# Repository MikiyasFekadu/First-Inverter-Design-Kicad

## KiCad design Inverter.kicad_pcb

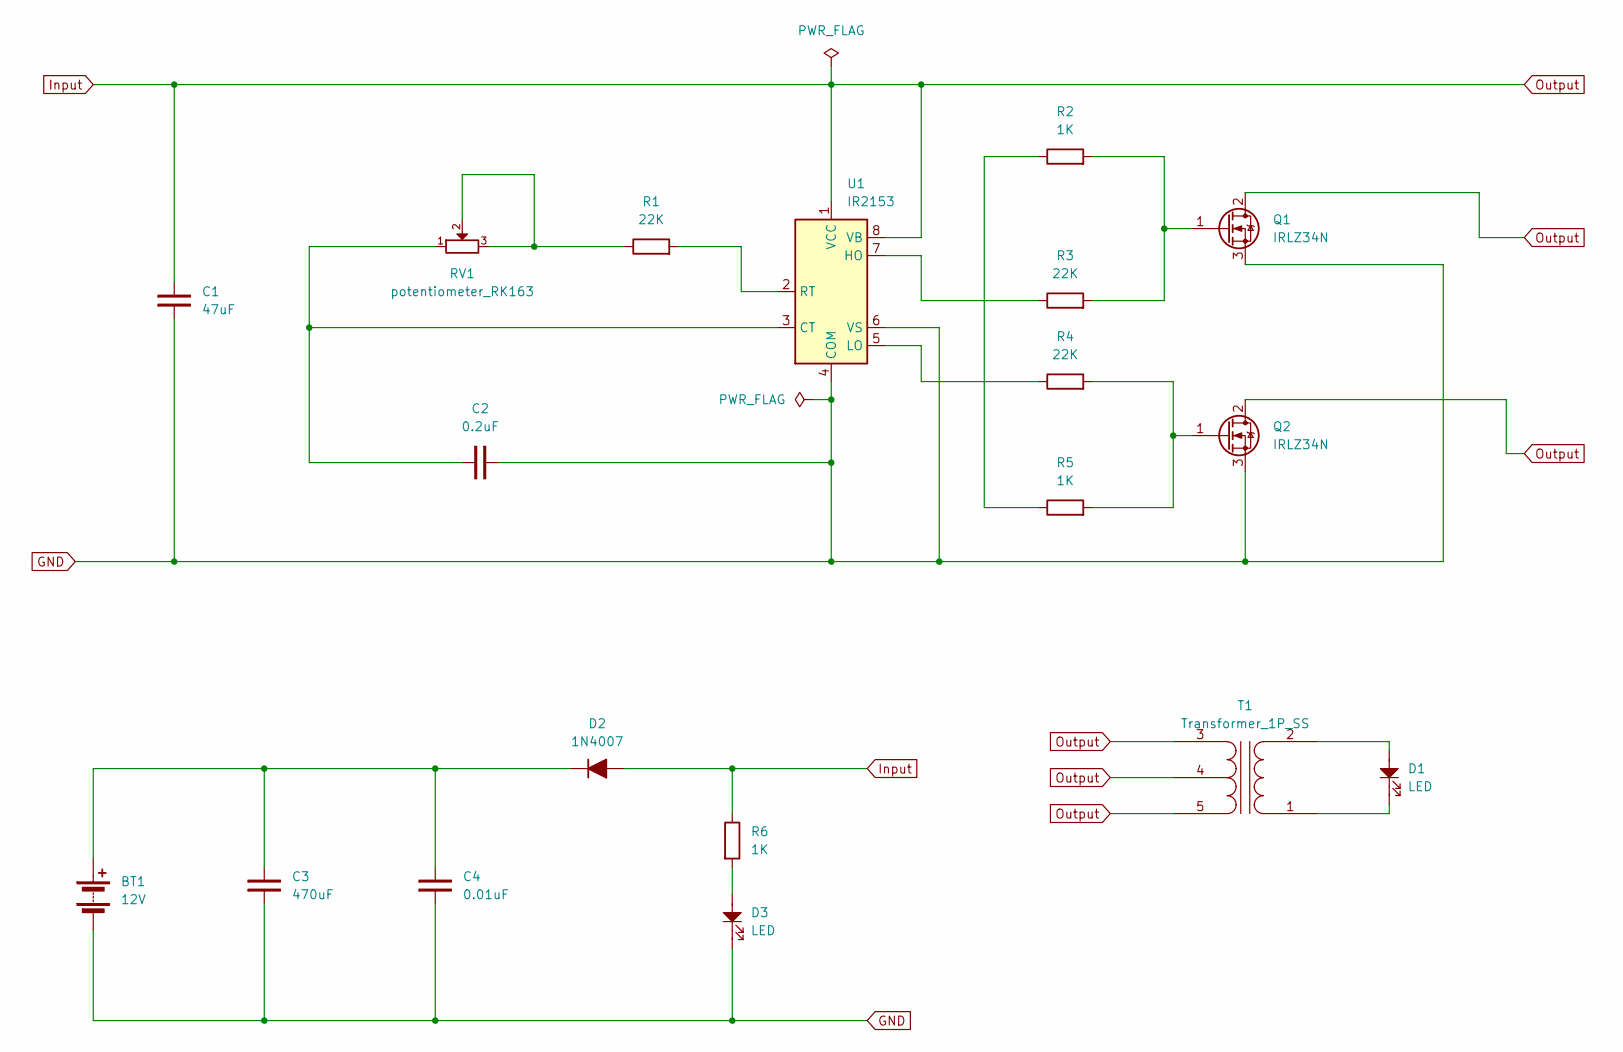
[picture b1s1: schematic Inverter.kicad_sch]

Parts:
BT1: 12V; TerminalBlock_Xinya_XY308-2.54-2P_1x02_P2.54mm_Horizontal
C1: 47uF; CP_Radial_D4.0mm_P1.50mm
C2: 0.2uF; C_Disc_D3.0mm_W2.0mm_P2.50mm
C3: 470uF; CP_Radial_D4.0mm_P1.50mm
C4: 0.01uF; C_Disc_D3.0mm_W2.0mm_P2.50mm
D1, D3: LED; LED_D5.0mm
D2: 1N4007; D_DO-41_SOD81_P10.16mm_Horizontal
Q1, Q2: IRLZ34N; TO-220-3_Vertical
R1, R3, R4: 22K; R_Axial_DIN0204_L3.6mm_D1.6mm_P5.08mm_Horizontal
R2, R5, R6: 1K; R_Axial_DIN0204_L3.6mm_D1.6mm_P5.08mm_Horizontal
RV1: potentiometer_RK163; TRIM_3296W-1-250
T1: Transformer_1P_SS; DIP-8_W7.62mm
U1: IR2153; DIP-8_W7.62mm

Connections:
GND: BT1.2 (-), C1.1, C2.2, C3.1, C4.1, D3.1, Q1.3 (S), Q2.3 (S), U1.4 (COM), U1.6 (VS)
Input: C1.2, D2.2 (A), Q1.2 (D), Q2.2 (D), R6.1, T1.3 (SA), T1.4 (SC), T1.5 (SB), U1.1 (VCC), U1.8 (VB)
unnamed: BT1.1 (+), C3.2, C4.2, D2.1 (K)
unnamed: D3.2, R6.2
unnamed: Q1.1 (G), R2.2, R3.2
unnamed: Q2.1 (G), R4.2, R5.2
unnamed: R1.1, RV1.2, RV1.3
unnamed: R2.1, R5.1
unnamed: D1.1, T1.1 (AA)
unnamed: D1.2, T1.2 (AB)
unnamed: C2.1, RV1.1, U1.3 (CT)
unnamed: R3.1, U1.7 (HO)
unnamed: R4.1, U1.5 (LO)
unnamed: R1.2, U1.2 (RT)

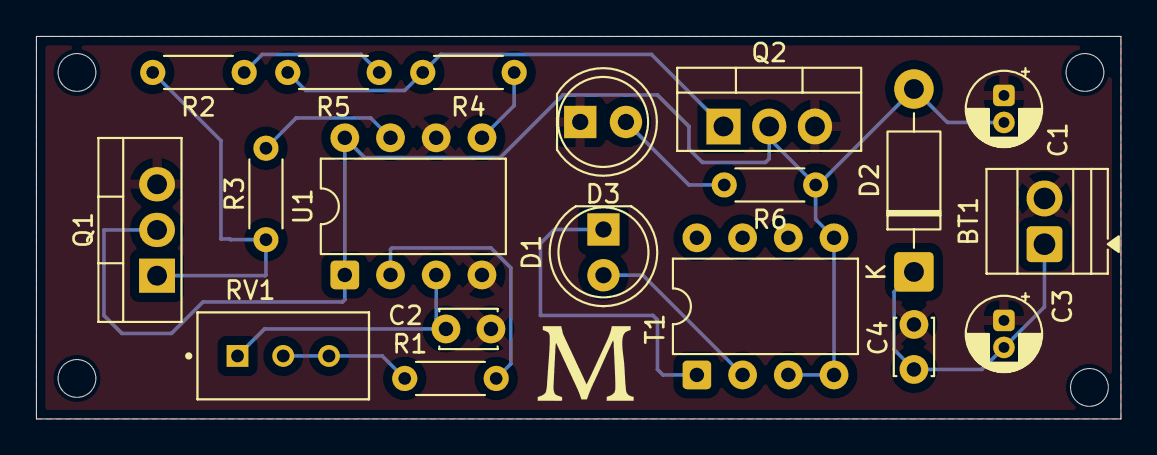
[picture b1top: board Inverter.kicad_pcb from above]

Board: 2 copper layers, 60.2 x 21.2 mm, 19 parts (0 on the bottom side), 14 nets.

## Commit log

2026-03-06 Initial commit - Project 1 KiCad zip
2026-03-06 Upload Inverter KiCad project files
2026-03-06 Remove old Project1.zip from repo
2026-03-06 Upload Inverter project files
2026-03-08 Added into Github Desktops
